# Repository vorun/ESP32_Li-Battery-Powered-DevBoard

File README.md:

# ESP32_Li-Battery-Powered-DevBoard

Esp32 development board that can be powered by 1S(3.7V) li-po battery with built in charger circuit to charge the battery from micro usb port.

- Green led at the left bottom of the board lights up when the battery is being charged. Board can be powered from micro usb port without the battery.

- Battery charge level can be monitored from GPIO35 pin.

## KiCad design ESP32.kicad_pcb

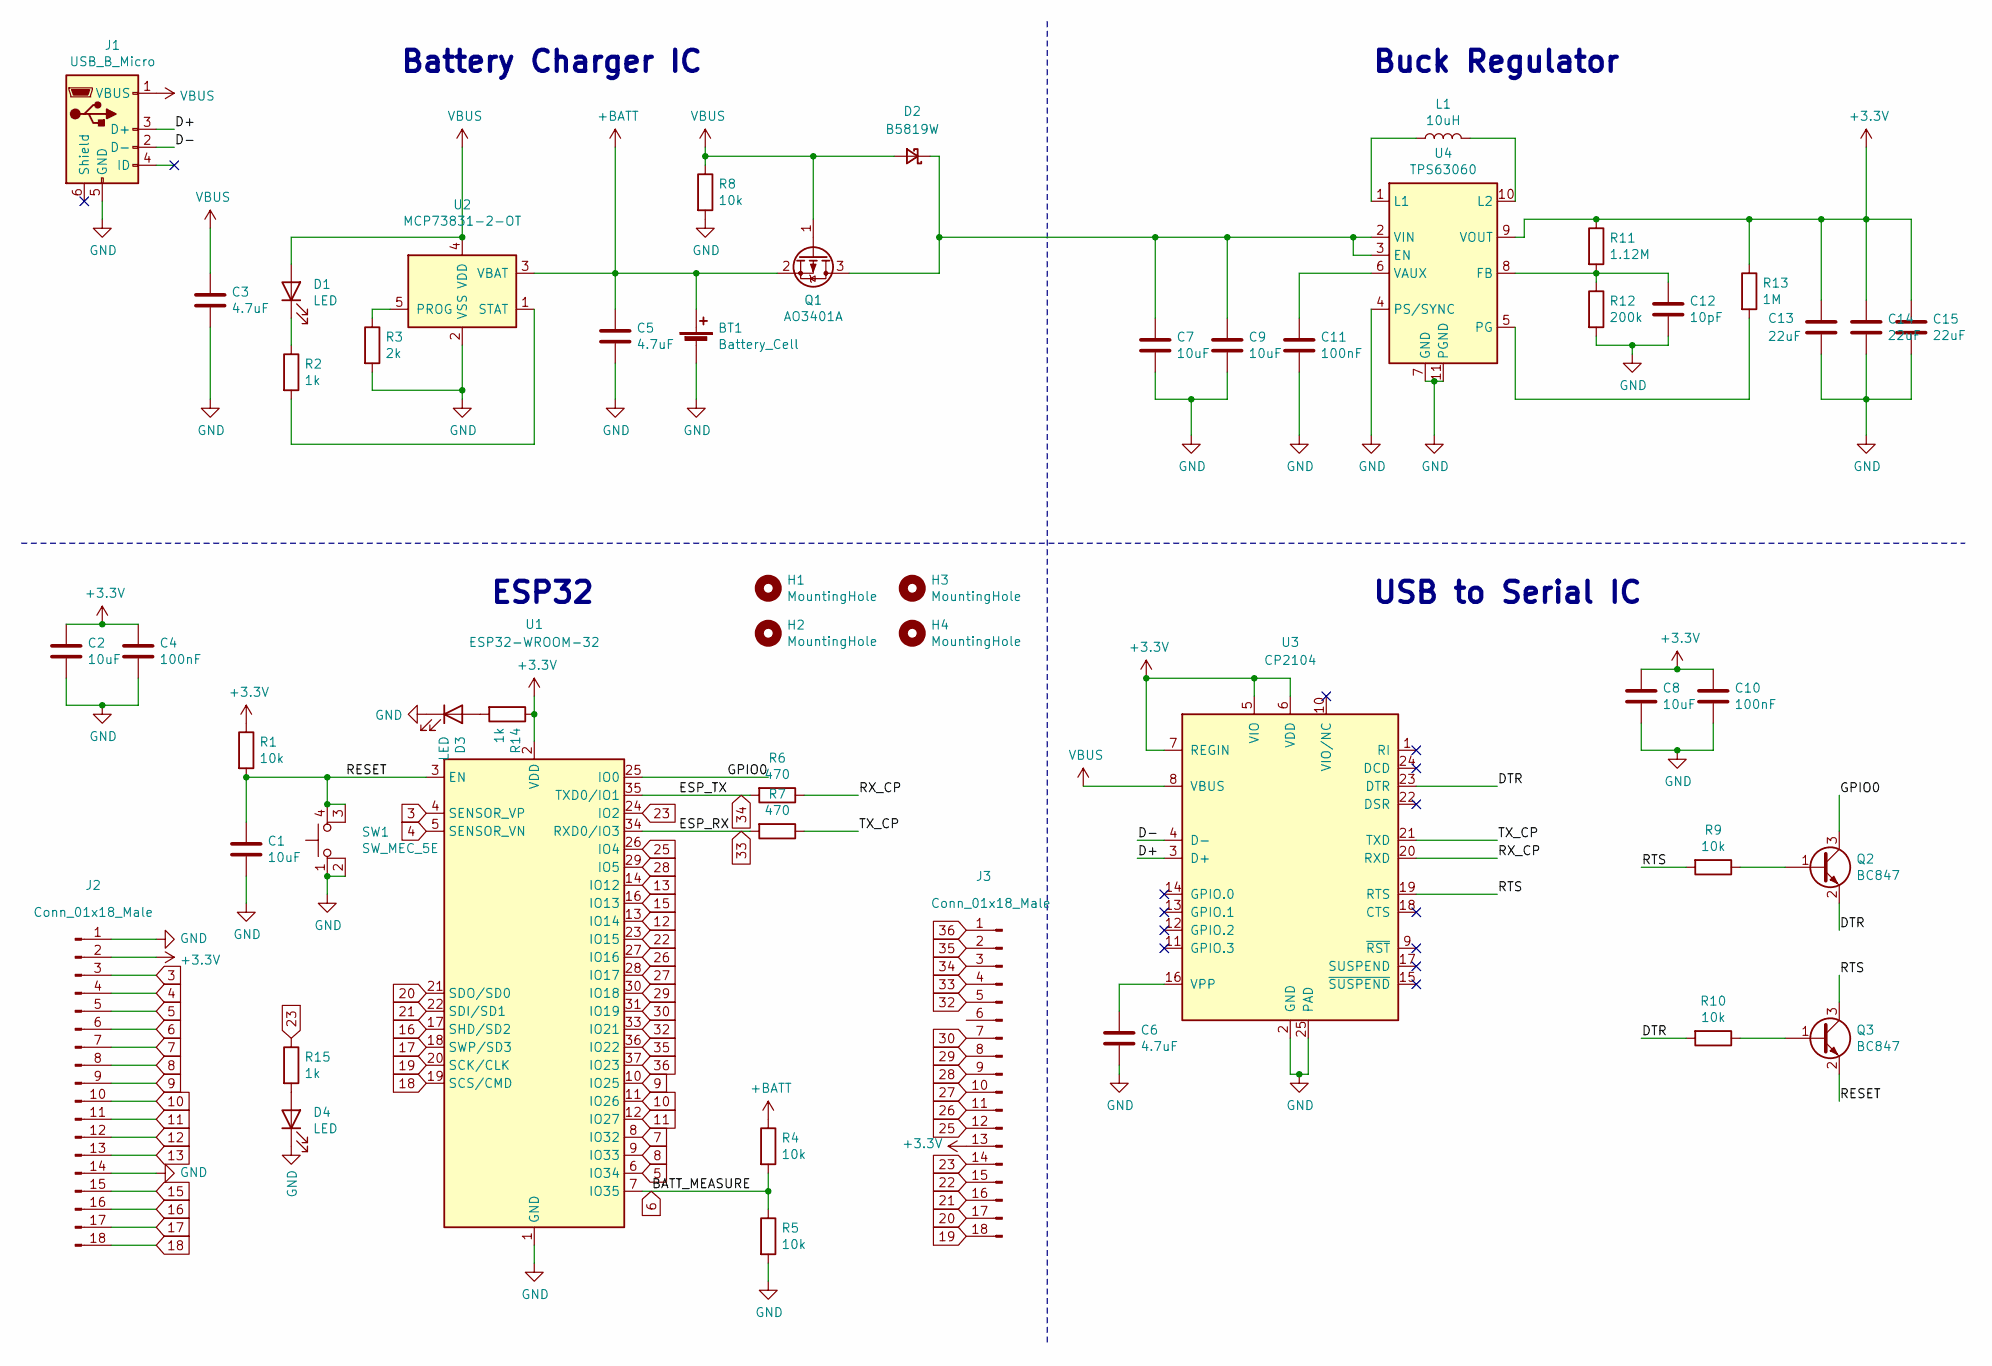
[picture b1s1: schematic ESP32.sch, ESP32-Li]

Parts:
BT1: Battery_Cell; JST_EH_S2B-EH_1x02_P2.50mm_Horizontal
C1, C2, C8: 10uF; C_0402_1005Metric
C3, C5: 4.7uF; C_1206_3216Metric
C4, C10, C11: 100nF; C_0402_1005Metric
C6: 4.7uF; C_0402_1005Metric
C7, C9: 10uF; C_1206_3216Metric
C12: 10pF; C_0402_1005Metric
C13, C14, C15: 22uF; C_0603_1608Metric
D1, D3, D4: LED; LED_0603_1608Metric
D2: B5819W; D_SOD-123
H1, H2, H3, H4: MountingHole; MountingHole_2.2mm_M2_Pad_Via
J1: USB_B_Micro; USB_Micro-B_Amphenol_10104110_Horizontal
J2, J3: Conn_01x18_Male; PinHeader_1x18_P2.54mm_Vertical
L1: 10uH; L_Sunlord_MWSA0518_5.4x5.2mm
Q1: AO3401A; SOT-23
Q2, Q3: BC847; SOT-23
R1, R8: 10k; R_0603_1608Metric
R2, R14, R15: 1k; R_0603_1608Metric
R3: 2k; R_0603_1608Metric
R4, R5, R9, R10: 10k; R_0402_1005Metric
R6, R7: 470; R_0402_1005Metric
R11: 1.12M; R_0603_1608Metric
R12: 200k; R_0603_1608Metric
R13: 1M; R_0603_1608Metric
SW1: SW_MEC_5E; SW_Push_1P1T_NO_CK_KMR2
U1: ESP32-WROOM-32
U2: MCP73831-2-OT; SOT-23-5
U3: CP2104; QFN-24-1EP_4x4mm_P0.5mm_EP2.6x2.6mm
U4: TPS63060; Texas_S-PWSON-N10_ThermalVias

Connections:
3: J2.3, U1.4 (SENSOR_VP)
4: J2.4, U1.5 (SENSOR_VN)
5: J2.5, U1.6 (IO34)
6: J2.6, R4.2, R5.1, U1.7 (IO35)
7: J2.7, U1.8 (IO32)
8: J2.8, U1.9 (IO33)
9: J2.9, U1.10 (IO25)
10: J2.10, U1.11 (IO26)
11: J2.11, U1.12 (IO27)
12: J2.12, U1.13 (IO14)
13: J2.13, U1.14 (IO12)
15: J2.15, U1.16 (IO13)
16: J2.16, U1.17 (SHD/SD2)
17: J2.17, U1.18 (SWP/SD3)
18: J2.18, U1.19 (SCS/CMD)
19: J3.18, U1.20 (SCK/CLK)
20: J3.17, U1.21 (SDO/SD0)
21: J3.16, U1.22 (SDI/SD1)
22: J3.15, U1.23 (IO15)
23: J3.14, R15.1, U1.24 (IO2)
25: J3.12, U1.26 (IO4)
26: J3.11, U1.27 (IO16)
27: J3.10, U1.28 (IO17)
28: J3.9, U1.29 (IO5)
29: J3.8, U1.30 (IO18)
30: J3.7, U1.31 (IO19)
32: J3.5, U1.33 (IO21)
33: J3.4, R7.2, U1.34 (RXD0/IO3)
34: J3.3, R6.2, U1.35 (TXD0/IO1)
35: J3.2, U1.36 (IO22)
36: J3.1, U1.37 (IO23)
+3V3: C2.1, C4.1, C8.1, C10.1, C13.1, C14.1, C15.1, J2.2, J3.13, R1.1, R11.1, R13.1, R14.1, U1.2 (VDD), U3.5 (VIO), U3.6 (VDD), U3.7 (REGIN), U4.9 (VOUT)
+BATT: BT1.1 (+), C5.1, Q1.2 (S), R4.1, U2.3 (VBAT)
/D+: J1.3 (D+), U3.3 (D+)
/D-: J1.2 (D-), U3.4 (D-)
/DTR: Q2.2 (E), R10.2, U3.23 (DTR)
/GPIO0: Q2.3 (C), U1.25 (IO0)
/RESET: C1.1, Q3.2 (E), R1.2, SW1.3 (K), SW1.4 (A), U1.3 (EN)
/RTS: Q3.3 (C), R9.2, U3.19 (RTS)
/RX_CP: R6.1, U3.20 (RXD)
/TX_CP: R7.1, U3.21 (TXD)
GND: BT1.2 (-), C1.2, C2.2, C3.2, C4.2, C5.2, C6.2, C7.2, C8.2, C9.2, C10.2, C11.2, C12.2, C13.2, C14.2, C15.2, D3.1 (K), D4.1 (K), J1.5 (GND), J2.1, J2.14, R3.2, R5.2, R8.2, R12.2, SW1.1, SW1.2, U1.1 (GND), U1.15 (GND), U1.38 (GND), U1.39 (GND), U2.2 (VSS), U3.2 (GND), U3.25 (PAD), U4.4 (PS/SYNC), U4.7 (GND), U4.11 (PGND)
unnamed: C6.1, U3.16 (VPP)
unnamed: C7.1, C9.1, D2.1 (K), Q1.3 (D), U4.2 (VIN), U4.3 (EN)
unnamed: C11.1, U4.6 (VAUX)
unnamed: C12.1, R11.2, R12.1, U4.8 (FB)
unnamed: D1.1 (K), R2.1
unnamed: D3.2 (A), R14.2
unnamed: D4.2 (A), R15.2
unnamed: L1.1, U4.1 (L1)
unnamed: L1.2, U4.10 (L2)
unnamed: Q2.1 (B), R9.1
unnamed: Q3.1 (B), R10.1
unnamed: R2.2, U2.1 (STAT)
unnamed: R3.1, U2.5 (PROG)
unnamed: R13.2, U4.5 (PG)
VBUS: C3.1, D1.2 (A), D2.2 (A), J1.1 (VBUS), Q1.1 (G), R8.1, U2.4 (VDD), U3.8 (VBUS)

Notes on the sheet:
USB to Serial IC
ESP32
Battery Charger IC
Buck Regulator

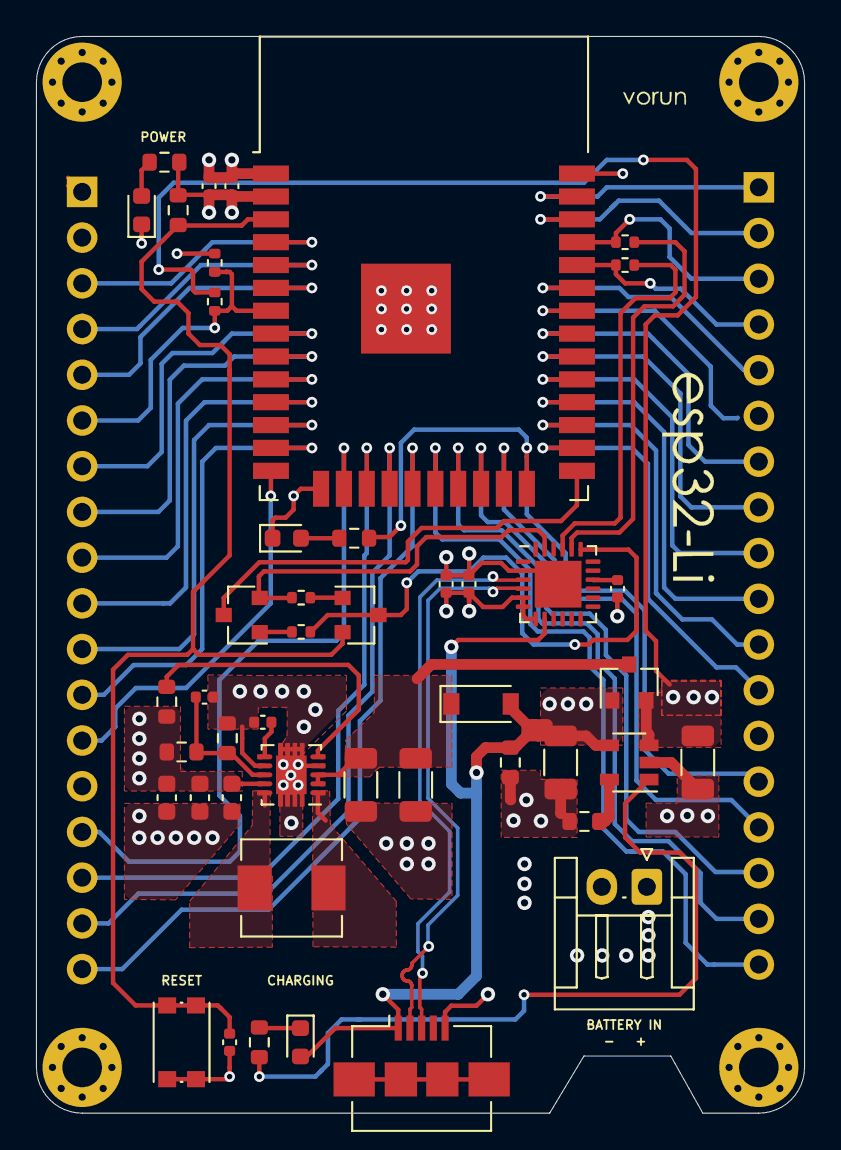
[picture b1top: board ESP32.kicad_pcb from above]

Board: 4 copper layers, 42.7 x 59.8 mm, 51 parts (0 on the bottom side), 57 nets.

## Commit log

2022-06-29 Schematic added
